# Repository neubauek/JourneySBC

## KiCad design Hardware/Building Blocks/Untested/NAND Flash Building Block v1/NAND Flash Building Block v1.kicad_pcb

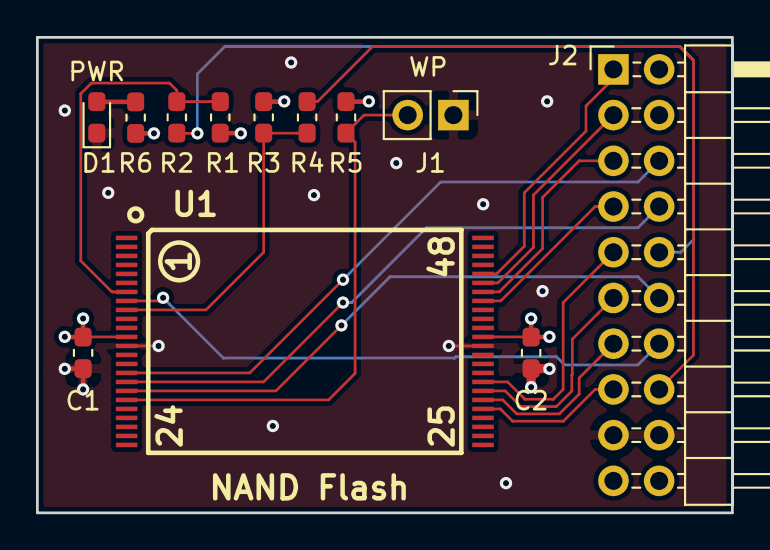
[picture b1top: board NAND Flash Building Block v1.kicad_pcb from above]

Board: 4 copper layers, 38.6 x 26.4 mm, 12 parts (0 on the bottom side), 20 nets.

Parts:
C1, C2: 0.1uF; C_0603_1608Metric_Pad1.05x0.95mm_HandSolder
D1: PWR; LED_0603_1608Metric_Pad1.05x0.95mm_HandSolder
J1: WP; PinHeader_1x02_P2.54mm_Vertical
J2: Conn_02x10_Counter_Clockwise; PinHeader_2x10_P2.54mm_Horizontal
R1, R3, R5: 10K; R_0603_1608Metric_Pad1.05x0.95mm_HandSolder
R2, R4: R0; R_0603_1608Metric_Pad1.05x0.95mm_HandSolder
R6: 330; R_0603_1608Metric_Pad1.05x0.95mm_HandSolder
U1: NAND Flash; TSOP48

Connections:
+3V3: C1.1, C2.1, J2.19, J2.20, R1.1, R3.1, R5.1, R6.1, U1.12, U1.37
/ALE: J2.8, U1.17
/CE: J2.16, R4.1
/CLE: J2.6, U1.16
/IO0: J2.15, U1.29
/IO1: J2.13, U1.30
/IO2: J2.11, U1.31
/IO3: J2.9, U1.32
/IO4: J2.7, U1.41
/IO5: J2.5, U1.42
/IO6: J2.3, U1.43
/IO7: J2.1, U1.44
/RB: J2.10, R2.1
/RE: J2.14, U1.8
/WE: J2.12, U1.18
GND: C1.2, C2.2, D1.1, J1.1, J2.17, J2.18, U1.13, U1.36
unnamed: D1.2, R6.2
unnamed: J1.2, R5.2, U1.19
unnamed: R1.2, R2.2, U1.7
unnamed: R3.2, R4.2, U1.9

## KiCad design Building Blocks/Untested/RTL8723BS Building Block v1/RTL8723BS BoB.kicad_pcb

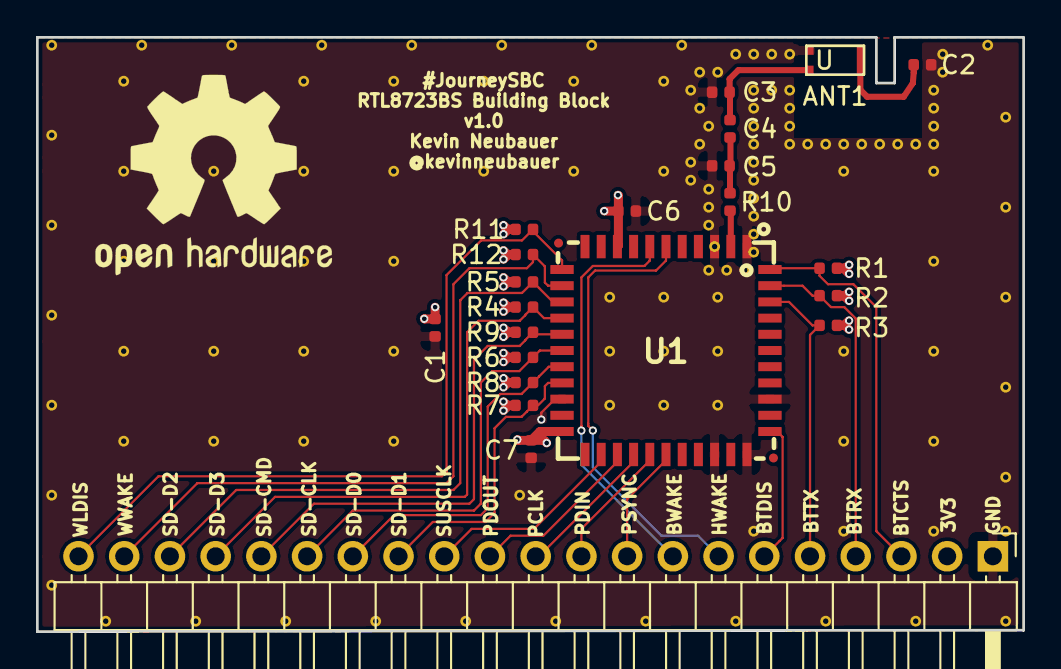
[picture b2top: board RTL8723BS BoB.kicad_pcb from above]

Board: 4 copper layers, 54.8 x 33.0 mm, 21 parts (0 on the bottom side), 17 nets.

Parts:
ANT1: AA055A
C1: 1uF; C_0402_1005Metric
C2: 0.9pF; C_0402_1005Metric
C3: NC; C_0402_1005Metric
C4: 4.3pF; C_0402_1005Metric
C5: 1.2pF; C_0402_1005Metric
C6: 10uF; C_0402_1005Metric
C7: 4.7uF; C_0402_1005Metric
R1, R6: NC; R_0402_1005Metric
R2, R3, R11, R12: 10K; R_0402_1005Metric
R4, R5, R7, R8, R9: 33K; R_0402_1005Metric
R10: 0R; R_0402_1005Metric
U1: RTL8723BS(ComboModule); RL-SM02BD(RTL8723BS)

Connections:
+3V3: C1.2, C6.2, C7.2, R1.2, R2.2, R3.2, R4.1, R5.1, R6.1, R7.1, R8.1, R9.1, R11.1, R12.1, U1.9, U1.22
/BT-UART-CTS: R1.1, U1.44
/BT-UART-RX: R2.1, U1.43
/BT-UART-TX: R3.1, U1.42
/WL-DIS: R11.2, U1.12
/WL-HOST-WAKE: R12.2, U1.13
/WL-SDIO-CLK: R6.2, U1.17
/WL-SDIO-CMD: R9.2, U1.16
/WL-SDIO-D0: R8.2, U1.18
/WL-SDIO-D1: R7.2, U1.19
/WL-SDIO-D2: R5.2, U1.14
/WL-SDIO-D3: R4.2, U1.15
GND: ANT1.2, C1.1, C2.1, C3.2, C5.2, C6.1, C7.1, U1.1, U1.3, U1.20, U1.31, U1.33, U1.36
unnamed: ANT1.1, C3.1, C4.2
unnamed: ANT1.3, C2.2
unnamed: C4.1, C5.1, R10.2
unnamed: R10.1, U1.2

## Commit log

2018-11-17 V1 of RTL8723 Building Block
2018-11-17 Created Hardware folder
2018-11-25 NAND Flash Building Block v1
